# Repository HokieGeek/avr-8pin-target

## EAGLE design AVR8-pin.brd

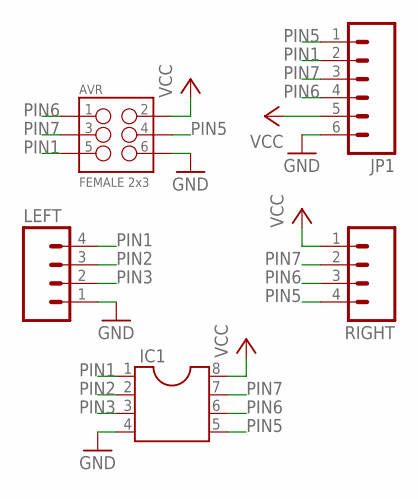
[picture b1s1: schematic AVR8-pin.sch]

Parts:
AVR: FEMALE 2x3; 2X3
IC1: DIL8; DIL08
JP1: M06SILK_FEMALE_PTH; 1X06
LEFT: M04PTH; 1X04
RIGHT: M04PTH; 1X04

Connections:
GND: AVR.6, IC1.4, JP1.6, LEFT.1
PIN1: AVR.5, IC1.1, JP1.2, LEFT.4
PIN2: IC1.2, LEFT.3
PIN3: IC1.3, LEFT.2
PIN5: AVR.4, IC1.5, JP1.1, RIGHT.4
PIN6: AVR.1, IC1.6, JP1.4, RIGHT.3
PIN7: AVR.3, IC1.7, JP1.3, RIGHT.2
VCC: AVR.2, IC1.8, JP1.5, RIGHT.1

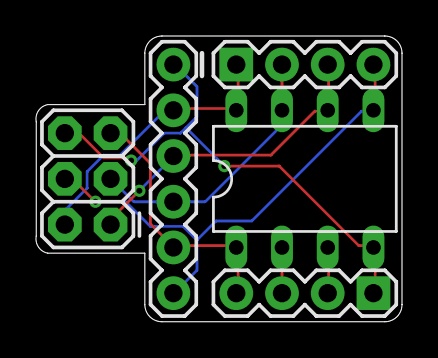
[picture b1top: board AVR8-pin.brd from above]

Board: 2 copper layers, 20.3 x 15.9 mm, 5 parts (0 on the bottom side), 8 nets.

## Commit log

2015-11-02 Initial commit... after ordering from OSHPark
2015-11-21 Oriented the AVR header correctly instead of the jacked up usbtinyisp cable
2015-11-22 Adjusted for a fix that was not a fix

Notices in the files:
parts and their libraries:
SparkFun-Connectors: Licensing: Creative Commons ShareAlike 4.0 International - https://creativecommons.org/licenses/by-sa/4.0
